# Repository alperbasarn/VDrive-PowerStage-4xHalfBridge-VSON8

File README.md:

# VDrive-PowerStage-4xHalfBridge-VSON8
Power stage carrier with 4 x half bridge configuration with mosfets with VSON-8 footprint

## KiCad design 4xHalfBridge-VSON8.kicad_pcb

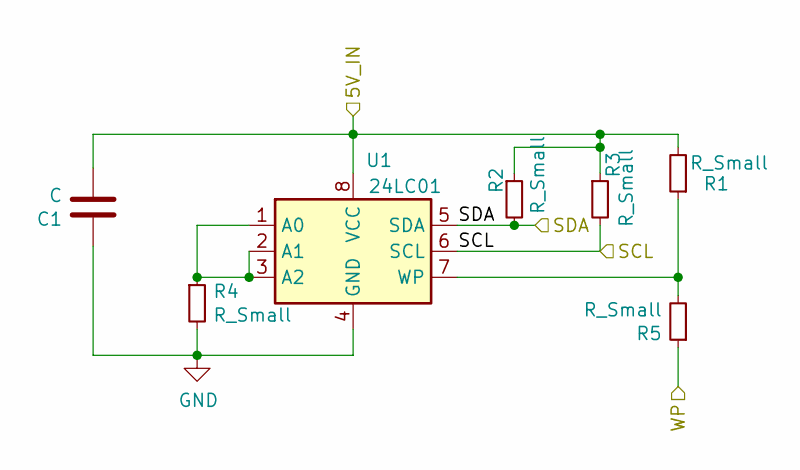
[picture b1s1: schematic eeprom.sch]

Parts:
C1: C; C_0402_1005Metric
R1, R2, R3, R4, R5: R_Small; R_0402_1005Metric
U1: 24LC01; DFN-8-1EP_3x2mm_P0.5mm_EP1.75x1.45mm

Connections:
/CarrierBoard/5V: C1.1, R1.2, R2.1, R3.1, U1.8 (VCC); also elsewhere on the board
/CarrierBoard/EEPROM_SCL: R3.2, U1.6 (SCL); also elsewhere on the board
/CarrierBoard/EEPROM_SDA: R2.2, U1.5 (SDA); also elsewhere on the board
/CarrierBoard/EEPROM_WP: R5.1; also elsewhere on the board
GND: C1.2, R4.2, U1.4 (GND); also elsewhere on the board
unnamed: R1.1, R5.2, U1.7 (WP)
unnamed: R4.1, U1.1 (A0), U1.2 (A1), U1.3 (A2)

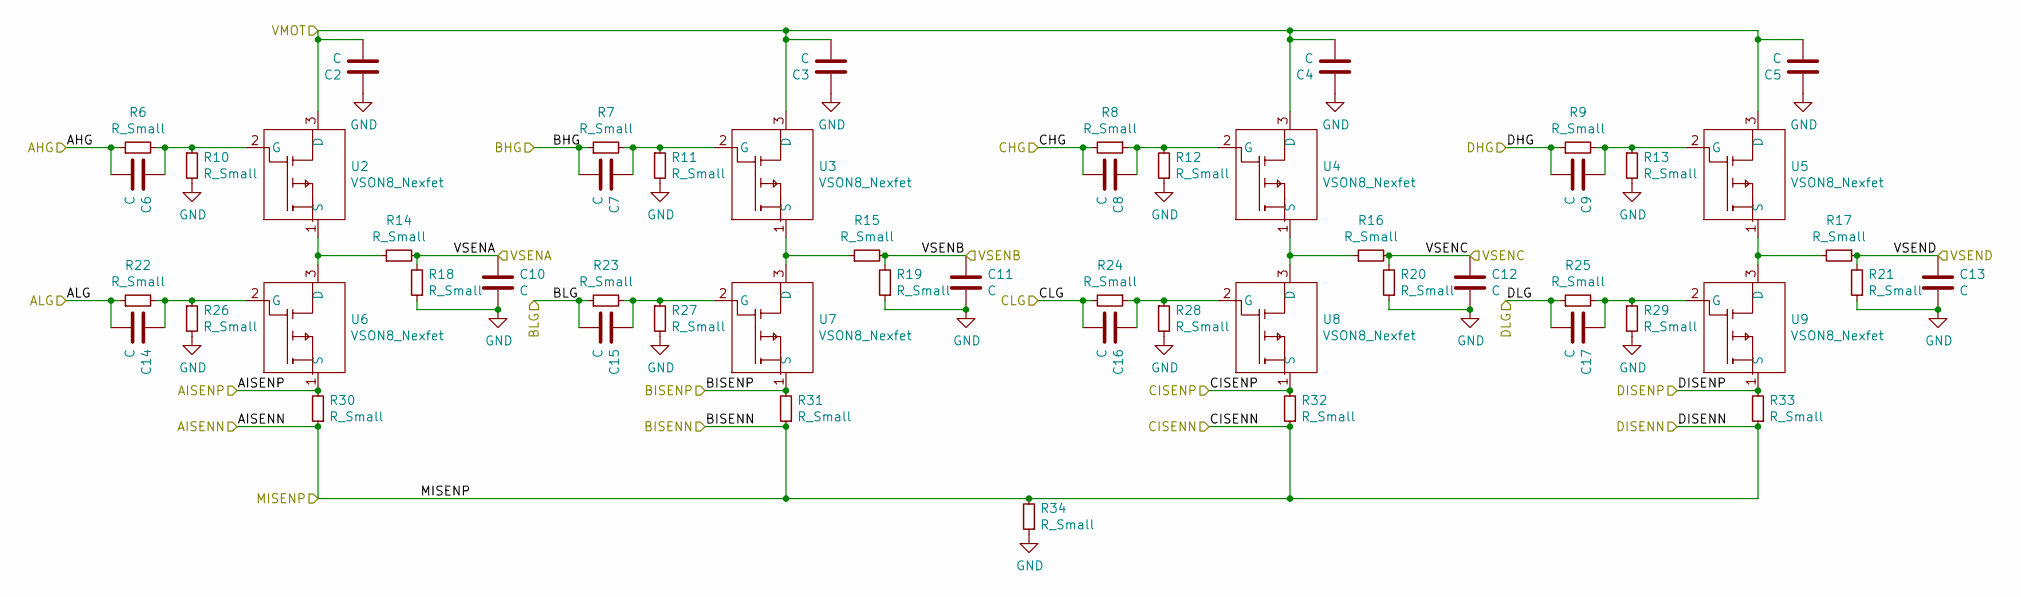
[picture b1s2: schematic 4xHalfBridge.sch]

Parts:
C2, C3, C4, C5: C; CP_Radial_D5.0mm_P2.00mm
C6, C7, C8, C9, C10, C11, C12, C13, C14, C15, C16, C17: C; C_0402_1005Metric
R6, R7, R8, R9, R10, R11, R12, R13, R14, R15, R16, R17, R22, R23, R24, R25, R26, R27, R28, R29: R_Small; R_0603_1608Metric
R18, R19, R20, R21: R_Small; R_0402_1005Metric
R30, R31, R32, R33, R34: R_Small; R_1210_3225Metric
U2, U3, U4, U5, U6, U7, U8, U9: VSON8_Nexfet; MOSFET_CSD19531Q5A

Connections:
/4xHalfBridge/AHG: C6.1, R6.1; also elsewhere on the board
/4xHalfBridge/AISENN: R30.1, R31.1, R32.1, R33.1, R34.2
/4xHalfBridge/AISENP: R30.2, U6.1 (S); also elsewhere on the board
/4xHalfBridge/ALG: C14.1, R22.1; also elsewhere on the board
/4xHalfBridge/BHG: C7.1, R7.1; also elsewhere on the board
/4xHalfBridge/BISENP: R31.2, U7.1 (S); also elsewhere on the board
/4xHalfBridge/BLG: C15.1, R23.1; also elsewhere on the board
/4xHalfBridge/CHG: C8.1, R8.2; also elsewhere on the board
/4xHalfBridge/CISENP: R32.2, U8.1 (S); also elsewhere on the board
/4xHalfBridge/CLG: C16.1, R24.2; also elsewhere on the board
/4xHalfBridge/DHG: C9.1, R9.1; also elsewhere on the board
/4xHalfBridge/DISENP: R33.2, U9.1 (S); also elsewhere on the board
/4xHalfBridge/DLG: C17.1, R25.1; also elsewhere on the board
/4xHalfBridge/VMOT: C2.1, C3.1, C4.1, C5.1, U2.3 (D), U3.3 (D), U4.3 (D), U5.3 (D); also elsewhere on the board
/4xHalfBridge/VSENA: C10.2, R14.2, R18.2; also elsewhere on the board
/4xHalfBridge/VSENB: C11.2, R15.2, R19.2; also elsewhere on the board
/4xHalfBridge/VSENC: C12.2, R16.2, R20.2; also elsewhere on the board
/4xHalfBridge/VSEND: C13.2, R17.1, R21.2; also elsewhere on the board
GND: C2.2, C3.2, C4.2, C5.2, C10.1, C11.1, C12.1, C13.1, R10.2, R11.2, R12.1, R13.2, R18.1, R19.1, R20.1, R21.1, R26.2, R27.2, R28.2, R29.2, R34.1; also elsewhere on the board
unnamed: C6.2, R6.2, R10.1, U2.2 (G)
unnamed: C7.2, R7.2, R11.1, U3.2 (G)
unnamed: C8.2, R8.1, R12.2, U4.2 (G)
unnamed: C9.2, R9.2, R13.1, U5.2 (G)
unnamed: C14.2, R22.2, R26.1, U6.2 (G)
unnamed: C15.2, R23.2, R27.1, U7.2 (G)
unnamed: C16.2, R24.1, R28.1, U8.2 (G)
unnamed: C17.2, R25.2, R29.1, U9.2 (G)
unnamed: R14.1, U2.1 (S), U6.3 (D)
unnamed: R15.1, U3.1 (S), U7.3 (D)
unnamed: R16.1, U4.1 (S), U8.3 (D)
unnamed: R17.2, U5.1 (S), U9.3 (D)

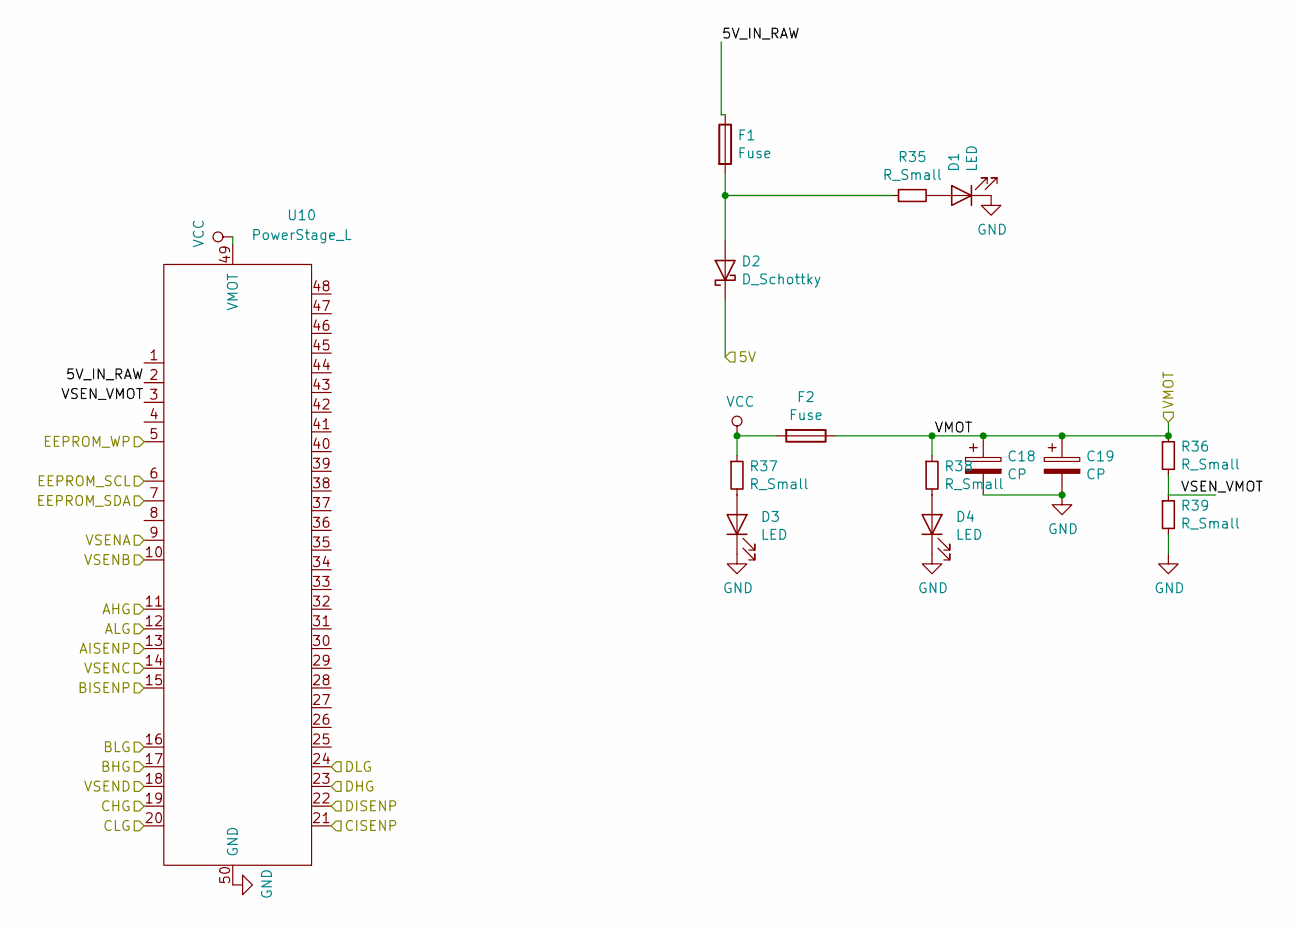
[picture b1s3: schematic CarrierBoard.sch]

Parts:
C18, C19: CP; CP_Radial_D10.0mm_P5.00mm
D1, D3, D4: LED; LED_0603_1608Metric_Pad1.05x0.95mm_HandSolder
D2: D_Schottky; D_0603_1608Metric_Pad1.05x0.95mm_HandSolder
F1: Fuse; Fuse_0603_1608Metric_Pad1.05x0.95mm_HandSolder
F2: Fuse; Fuse_1210_3225Metric_Pad1.42x2.65mm_HandSolder
R35, R36, R37, R38, R39: R_Small; R_0402_1005Metric
U10: PowerStage_L; PowerStage_Carrier_L

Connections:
/4xHalfBridge/AHG: U10.11; also elsewhere on the board
/4xHalfBridge/AISENP: U10.13; also elsewhere on the board
/4xHalfBridge/ALG: U10.12; also elsewhere on the board
/4xHalfBridge/BHG: U10.17; also elsewhere on the board
/4xHalfBridge/BISENP: U10.15; also elsewhere on the board
/4xHalfBridge/BLG: U10.16; also elsewhere on the board
/4xHalfBridge/CHG: U10.19; also elsewhere on the board
/4xHalfBridge/CISENP: U10.21; also elsewhere on the board
/4xHalfBridge/CLG: U10.20; also elsewhere on the board
/4xHalfBridge/DHG: U10.23; also elsewhere on the board
/4xHalfBridge/DISENP: U10.22; also elsewhere on the board
/4xHalfBridge/DLG: U10.24; also elsewhere on the board
/4xHalfBridge/VMOT: C18.1, C19.1, F2.1, R36.1, R38.1; also elsewhere on the board
/4xHalfBridge/VSENA: U10.9; also elsewhere on the board
/4xHalfBridge/VSENB: U10.10; also elsewhere on the board
/4xHalfBridge/VSENC: U10.14; also elsewhere on the board
/4xHalfBridge/VSEND: U10.18; also elsewhere on the board
/CarrierBoard/5V_IN_RAW: F1.1, U10.2
/CarrierBoard/EEPROM_SCL: U10.6; also elsewhere on the board
/CarrierBoard/EEPROM_SDA: U10.7; also elsewhere on the board
/CarrierBoard/EEPROM_WP: U10.5; also elsewhere on the board
/CarrierBoard/VSEN_VMOT: R36.2, R39.1, U10.3
GND: C18.2, C19.2, D1.1 (K), D3.1 (K), D4.1 (K), R39.2, U10.50 (GND); also elsewhere on the board
unnamed: D1.2 (A), R35.2
unnamed 35: D2.2 (A), F1.2, R35.1; also elsewhere on the board
unnamed: D3.2 (A), R37.2
unnamed: D4.2 (A), R38.2
VCC: F2.2, R37.1, U10.49 (VMOT)

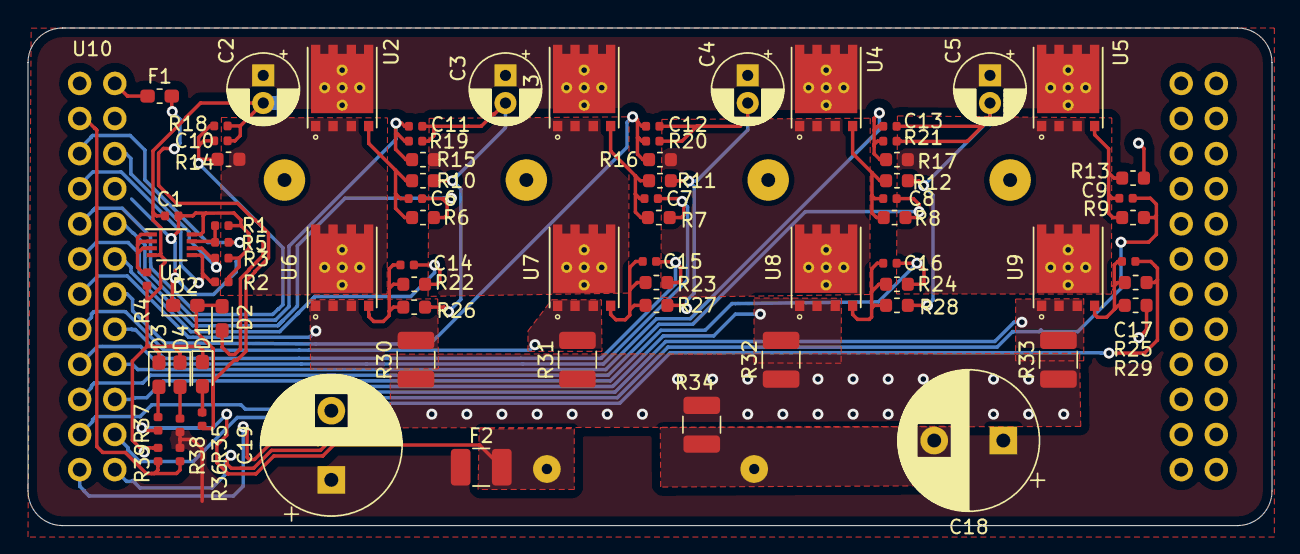
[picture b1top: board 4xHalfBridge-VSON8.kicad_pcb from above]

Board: 2 copper layers, 90.0 x 36.0 mm, 75 parts (0 on the bottom side), 44 nets.

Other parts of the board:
D2#2: D_Schottky; D_0603_1608Metric_Pad1.05x0.95mm_HandSolder

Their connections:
/CarrierBoard/5V: D2#2.1; also elsewhere on the board
unnamed 35: D2#2.2; also elsewhere on the board

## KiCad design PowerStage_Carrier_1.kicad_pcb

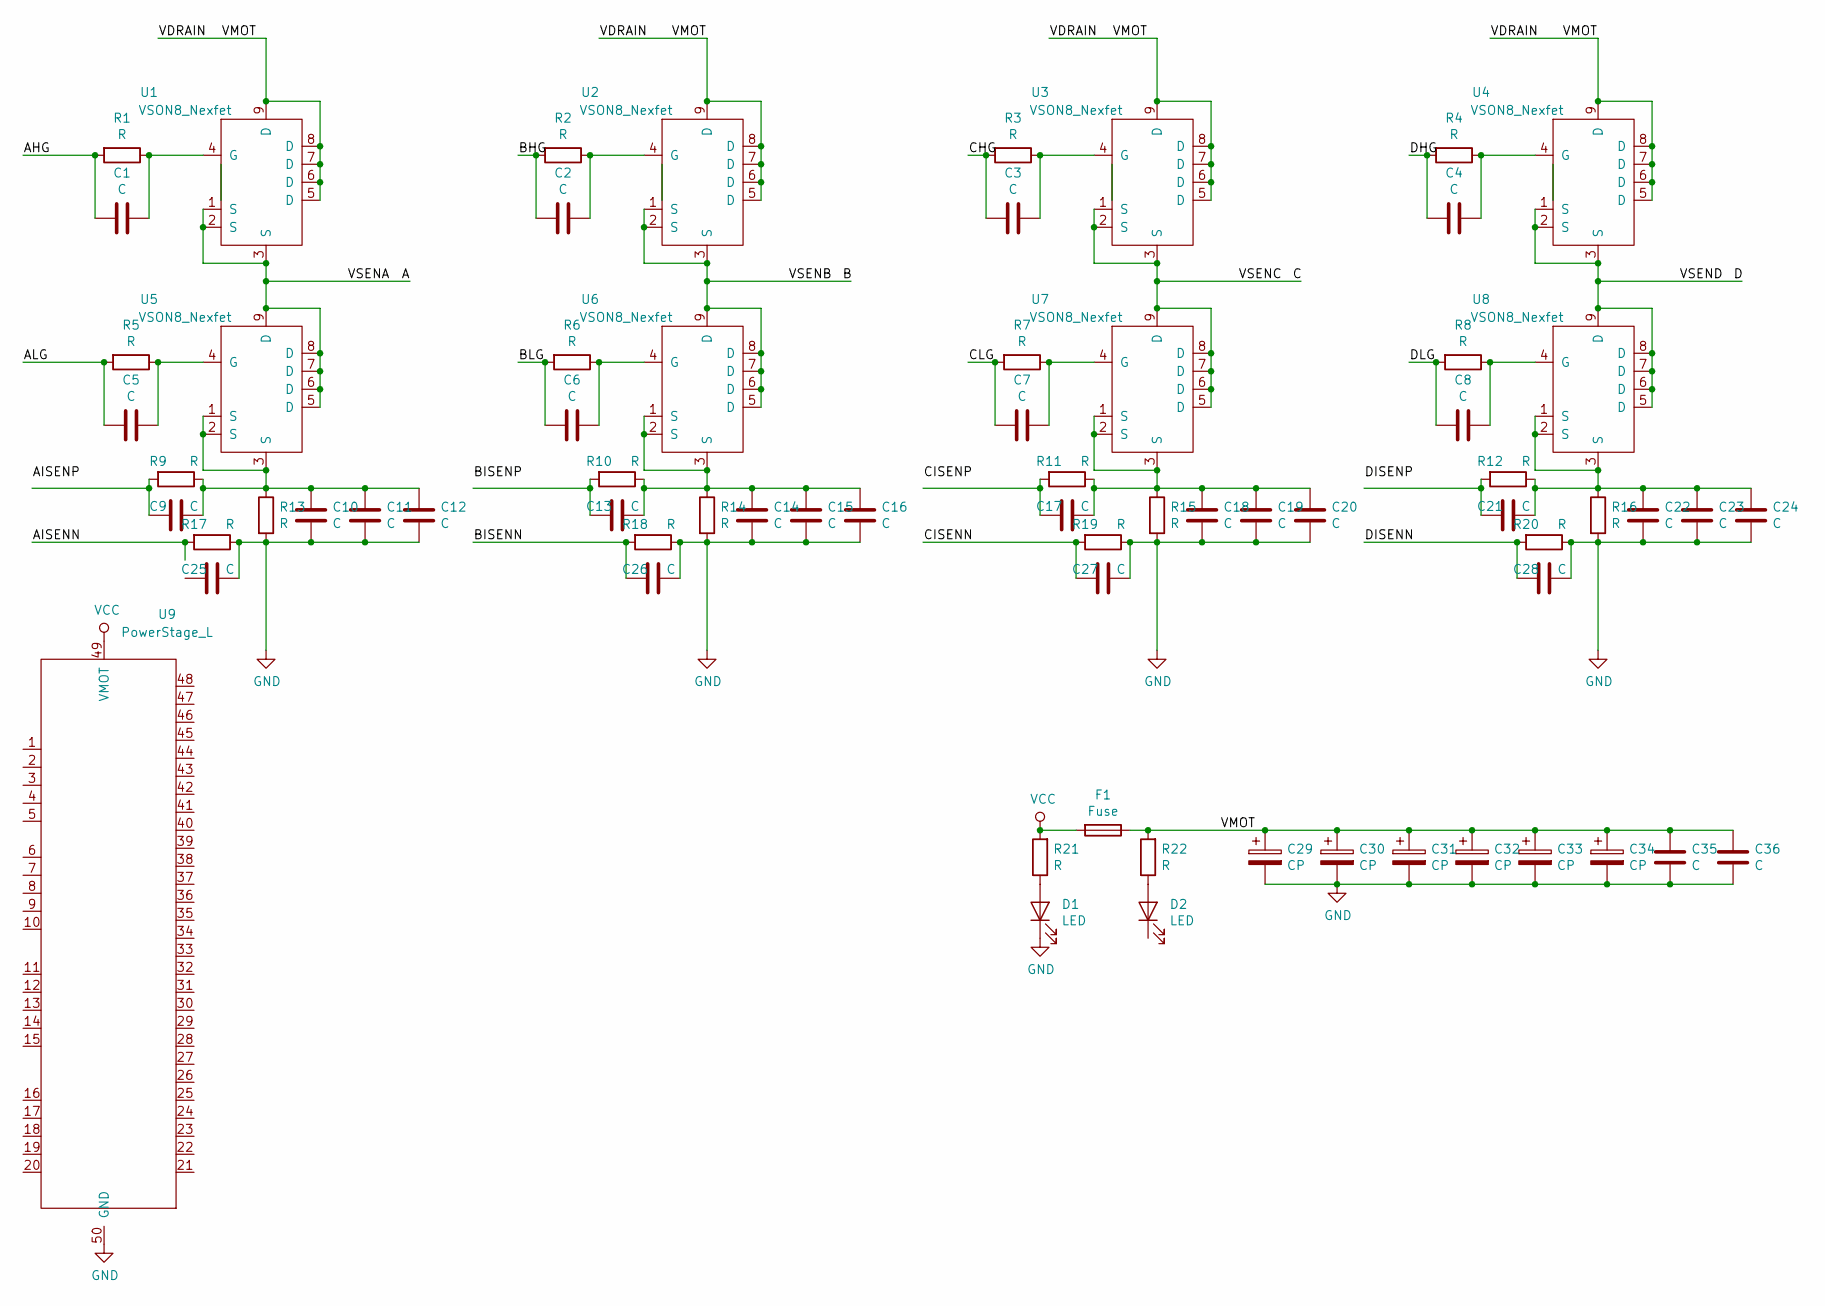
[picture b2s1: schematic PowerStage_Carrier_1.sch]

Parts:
C1, C2, C3, C4, C5, C6, C7, C8, C9, C10, C11, C12, C13, C14, C15, C16, C17, C18, C19, C20, C21, C22, C23, C24, C25, C26, C27, C28: C; C_0603_1608Metric_Pad1.05x0.95mm_HandSolder
C29, C30: CP; CP_Radial_D10.0mm_P5.00mm
C31, C32, C33, C34: CP; CP_Radial_D5.0mm_P2.50mm
C35: C; C_1206_3216Metric_Pad1.42x1.75mm_HandSolder
C36: C; C_0805_2012Metric_Pad1.15x1.40mm_HandSolder
D1, D2: LED; LED_0603_1608Metric_Pad1.05x0.95mm_HandSolder
F1: Fuse; Fuse_1210_3225Metric_Pad1.42x2.65mm_HandSolder
R1, R2, R3, R4, R5, R6, R7, R8, R9, R10, R11, R12, R17, R18, R19, R20, R21, R22: R; R_0603_1608Metric_Pad1.05x0.95mm_HandSolder
R13, R14, R15, R16: R; R_1806_4516Metric_Pad1.57x1.80mm_HandSolder
U1, U2, U3, U4, U5, U6, U7, U8: VSON8_Nexfet; MOSFET_CSD19531Q5A
U9: PowerStage_L; PowerStage_Carrier_L

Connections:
/A: U1.1 (S), U1.2 (S), U1.3 (S), U5.5 (D), U5.6 (D), U5.7 (D), U5.8 (D), U5.9 (D)
/AHG: C1.2, R1.2; also elsewhere on the board
/AISENN: R17.2
/ALG: C5.2, R5.2; also elsewhere on the board
/B: U2.1 (S), U2.2 (S), U2.3 (S), U6.5 (D), U6.6 (D), U6.7 (D), U6.8 (D), U6.9 (D)
/BHG: C2.2, R2.2
/BISENN: C26.2, R18.2
/BLG: C6.2, R6.2
/C: U3.1 (S), U3.2 (S), U3.3 (S), U7.5 (D), U7.6 (D), U7.7 (D), U7.8 (D), U7.9 (D)
/CHG: C3.2, R3.2; also elsewhere on the board
/CISENN: C27.2, R19.2
/CLG: C7.2, R7.2; also elsewhere on the board
/D: U4.1 (S), U4.2 (S), U4.3 (S), U8.5 (D), U8.6 (D), U8.7 (D), U8.8 (D), U8.9 (D)
/DHG: C4.2, R4.2; also elsewhere on the board
/DISENN: C28.2, R20.2
/DLG: C8.2, R8.2; also elsewhere on the board
/VDRAIN: C29.1, C30.1, C31.1, C32.1, C33.1, C34.1, C35.1, C36.1, F1.1, R22.2, U1.5 (D), U1.6 (D), U1.7 (D), U1.8 (D), U1.9 (D), U2.5 (D), U2.6 (D), U2.7 (D), U2.8 (D), U2.9 (D), U3.5 (D), U3.6 (D), U3.7 (D), U3.8 (D), U3.9 (D), U4.5 (D), U4.6 (D), U4.7 (D), U4.8 (D), U4.9 (D)
GND: C10.1, C11.1, C12.1, C14.1, C15.1, C16.1, C18.1, C19.1, C20.1, C22.1, C23.1, C24.1, C25.1, C26.1, C27.1, C28.1, C29.2, C30.2, C31.2, C32.2, C33.2, C34.2, C35.2, C36.2, D1.1 (K), R13.2, R14.2, R15.2, R16.2, R17.1, R18.1, R19.1, R20.1, U9.50 (GND)
unnamed: C1.1, R1.1, U1.4 (G)
unnamed: C2.1, R2.1, U2.4 (G)
unnamed: C3.1, R3.1, U3.4 (G)
unnamed: C4.1, R4.1, U4.4 (G)
unnamed: C5.1, R5.1, U5.4 (G)
unnamed: C6.1, R6.1, U6.4 (G)
unnamed: C7.1, R7.1, U7.4 (G)
unnamed: C8.1, R8.1, U8.4 (G)
unnamed: C9.2, R9.2
unnamed: C9.1, C10.2, C11.2, C12.2, R9.1, R13.1, U5.1 (S), U5.2 (S), U5.3 (S)
unnamed: C13.1, C14.2, C15.2, C16.2, R10.1, R14.1, U6.1 (S), U6.2 (S), U6.3 (S)
unnamed: C13.2, R10.2
unnamed: C17.1, C18.2, C19.2, C20.2, R11.1, R15.1, U7.1 (S), U7.2 (S), U7.3 (S)
unnamed: C17.2, R11.2
unnamed: C21.1, C22.2, C23.2, C24.2, R12.1, R16.1, U8.1 (S), U8.2 (S), U8.3 (S)
unnamed: C21.2, R12.2
unnamed: D1.2 (A), R21.1
unnamed: D2.2 (A), R22.1
VCC: F1.2, R21.2, U9.49 (VMOT)

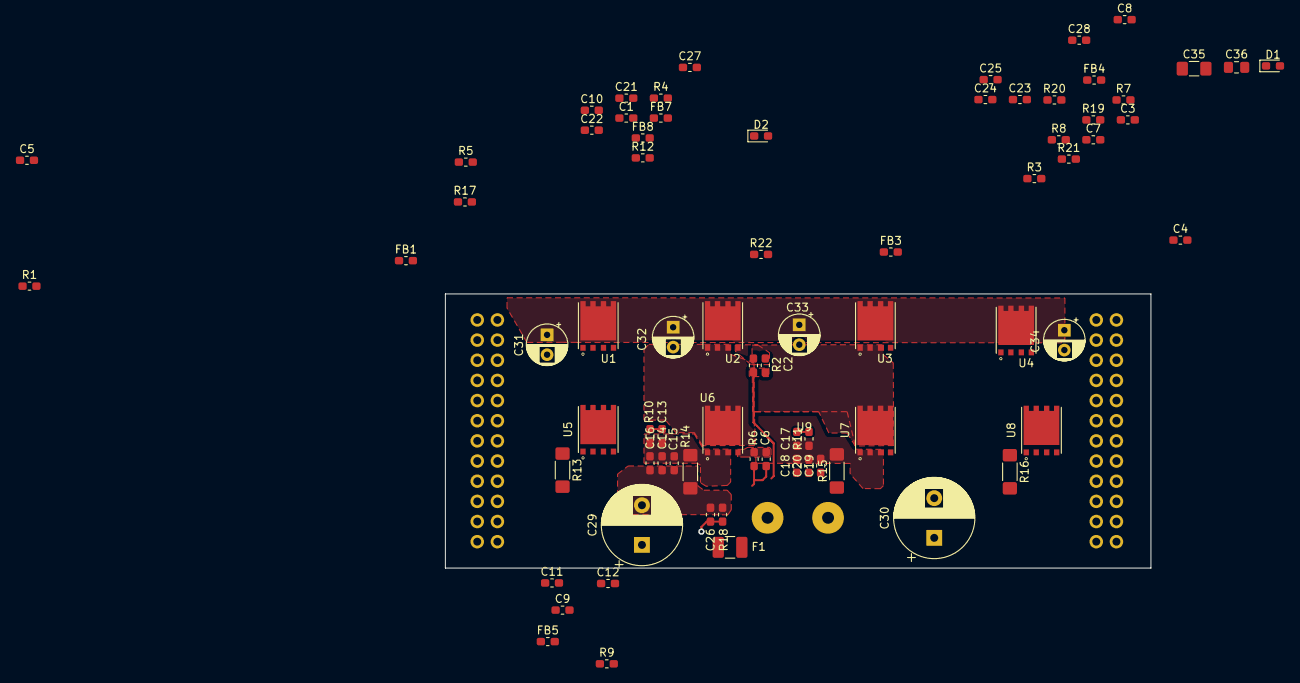
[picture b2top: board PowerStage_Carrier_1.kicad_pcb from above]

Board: 4 copper layers, 88.9 x 34.5 mm, 76 parts (0 on the bottom side), 36 nets.

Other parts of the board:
FB1, FB3, FB4, FB5, FB7, FB8: Ferrite_Bead; L_0603_1608Metric_Pad1.05x0.95mm_HandSolder

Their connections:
/AHG: FB1.2; also elsewhere on the board
/ALG: FB5.2; also elsewhere on the board
/CHG: FB3.2; also elsewhere on the board
/CLG: FB7.2; also elsewhere on the board
/DHG: FB4.2; also elsewhere on the board
/DLG: FB8.2; also elsewhere on the board

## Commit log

2021-07-17 add existing files to repo
2021-07-17 fix files
2021-07-17 remove leftover files
2021-07-17 continue routing
2021-07-18 finalize pcb without eeprom
2021-07-18 add eeprom.sch
2021-07-18 finalize schematic and PCB
2021-07-18 finalize schematic
2021-07-22 add voltage divider circuit for motor coil outpus
2021-07-31 re route pcb-re arrange schematics
2021-07-31 add files
2021-08-04 update eeprom resistor values
2021-08-04 update passive components values
